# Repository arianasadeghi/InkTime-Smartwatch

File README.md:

# InkTime - Open Source Smartwatch

InkTime este un proiect de smartwatch accesibil, open-source, conceput cu un accent puternic pe eficiența energetică și autonomia bateriei. Dispozitivul este construit în jurul ecosistemului nRF52840 (oferind conectivitate Bluetooth Low Energy) și folosește un ecran E-Ink pentru a asigura o vizibilitate excelentă în lumina soarelui cu un consum de energie aproape nul în stand-by.

Acest repository conține fișierele de design hardware pentru faza **EVT (Engineering Validation Test)**.

## 1. Diagrama Bloc a Sistemului

```mermaid
graph TD
    %% Power Management
    USB[Mufă USB-C / Pogo Pins] -->|5V| CHG[IC Încărcare BQ24040]
    CHG --> BATT[Acumulator LiPo 3.7V]
    BATT --> LDO[Regulator LDO 3.3V Ultra-Low Iq]
    
    %% Core
    LDO -.->|3.3V| MCU[SoC nRF52840]
    
    %% Interfaces & Peripherals
    MCU <-->|SPI| EINK[Display E-Ink 1.54]
    MCU <-->|I2C| IMU[Accelerometru BMA400]
    MCU <-->|I2C| HR[Senzor Puls MAX30102]
    MCU -->|GPIO| VIB[Motor Vibrații]
    MCU -->|GPIO| BTN[Butoane Navigare]
    
    %% Power lines
    LDO -.->|3.3V| EINK
    LDO -.->|3.3V| IMU
    LDO -.->|3.3V| HR
```

## 2. Bill Of Materials (BOM)

Tabelul de mai jos conține componentele principale folosite în designul plăcii. Lista completă (inclusiv rezistențe și condensatoare) se găsește în fișierul .csv din folderul Manufacturing.
| Componenta | Rol în sistem | JLC Part # | Link Datasheet |
| :--- | :--- | :--- | :--- |
| **nRF52840-QIAA** | Microcontroller principal (BLE, Cortex-M4F) | C206001 | [Datasheet nRF52840](https://infocenter.nordicsemi.com/pdf/nRF52840_PS_v1.7.pdf) |
    | **BQ24040DSQR** | IC Incarcare Acumulator LiPo (1A) | C43012 | [Datasheet BQ24040](https://www.ti.com/lit/ds/symlink/bq24040.pdf) |
| **TPS7A0533PDQNR** | LDO 3.3V (Consum Quiescent extrem de mic - 1µA) | C396492 | [Datasheet TPS7A05](https://www.ti.com/lit/ds/symlink/tps7a05.pdf) |
| **BMA400** | Accelerometru Ultra-Low Power (Pedometer) | C383215 | [Datasheet BMA400](https://www.bosch-sensortec.com/media/boschsensortec/downloads/datasheets/bst-bma400-ds000.pdf) |
| **MAX30102** | Senzor Optic Puls și SpO2 | C84666 | [Datasheet MAX30102](https://www.analog.com/media/en/technical-documentation/data-sheets/MAX30102.pdf) |
| **Ecran E-Ink 1.54 inch** | Display principal (SPI) | N/A (Modul) | [Datasheet Waveshare](https://www.waveshare.com/wiki/1.54inch_e-Paper_Module) |
## 3. Descrierea Functionalitatii Hardware

### Procesare si Conectivitate:
Inima ceasului InkTime este SoC-ul Nordic nRF52840. A fost ales datorita suportului nativ pentru Bluetooth 5.0 (BLE), esential pentru sincronizarea notificarilor cu telefonul mobil. Arhitectura ARM Cortex-M4F permite procesarea eficienta a algoritmilor de numarare a pasilor si calcul al ritmului cardiac.

### Managementul Consumului de Energie (Power Tree):
Fiind un dispozitiv wearable, constrângerile de baterie sunt critice.

Sistemul este alimentat de o baterie LiPo de mici dimensiuni (ex. 200mAh).

Încărcarea se face la 5V printr-un circuit BQ24040, reglat din rezistențe pentru a oferi un curent de încărcare mic și sigur (ex. 100mA).

Pentru a coborî tensiunea la 3.3V am folosit un LDO din seria TPS7A05, care are un curent de repaus (Iq) de doar 1µA, esențial pentru a nu drena bateria când ceasul este în Deep Sleep.

### Periferice și Interfețe:

Display-ul E-Ink: Comunică prin protocol SPI. Deși are un framerate mic, este perfect pentru un ceas deoarece consumă 0mA pentru a menține imaginea afișată.

Senzorii (IMU & HR): Comunicația se realizează pe o magistrală I2C partajată. BMA400 are un mod special de "step counter" hardware care poate trezi microcontroller-ul din sleep doar când utilizatorul face un pas, economisind masiv energia.

## 4. Alocarea Pinilor nRF52840

Microcontroller-ul nRF52840 permite maparea flexibilă a pinilor (orice funcție digitală pe orice pin), lucru care a facilitat o rutare curată (fără suprapuneri) pe PCB.
| Pin nRF52840 | Nume Net / Funcție | Justificare / Detalii |
| :--- | :--- | :--- |
| **P0.13 / P0.14 / P0.15** | `SPI_SCK`, `SPI_MOSI`, `SPI_MISO` | Magistrala SPI dedicată ecranului E-Ink. Pinii au fost aleși pe aceeași latură a chip-ului cu conectorul FPC al ecranului. |
| **P0.16** | `EINK_CS` (Chip Select) | Activare magistrală SPI pentru ecran. |
| **P0.17 / P0.18** | `EINK_DC`, `EINK_RST` | Pini de control adiționali (Data/Command și Reset) necesari controller-ului de E-Ink. |
| **P0.26 / P0.27** | `I2C_SDA`, `I2C_SCL` | Magistrala I2C pentru accelerometru (BMA400) și senzorul de puls (MAX30102). Conține rezistențe de pull-up de 4.7k. |
| **P1.02** | `IMU_INT` (Interrupt) | Pin setat ca Input. BMA400 trimite un semnal aici pentru a trezi SoC-ul când detectează mișcare. |
| **P1.06** | `MOTOR_PWM` | Pin configurat ca ieșire PWM, conectat la poarta unui tranzistor MOSFET N-Channel pentru a acționa motorul de vibrații (notificări haptice). |
| **P0.11 / P0.12** | `BTN_UP`, `BTN_DOWN` | Pini conectați la butoanele laterale, configurați cu Input Pull-Up intern. |
## 5. Design Log & Integrare Mecanică (EVT Phase)

### Construcția PCB-ului: 
Cablajul a fost realizat pe 2 straturi. Pentru a asigura performanța antenei, a fost respectată zona de keepout cerută în datasheet-ul antenei ceramice (sau PCB trace), neavând planuri de masă sub aceasta.

### Constrângeri Mecanice: 
Forma PCB-ului a fost dictată strict de fișierul .step al carcasei primite. Decupajele plăcii se aliniază perfect cu pinii de montare ai carcasei.

### Stack-up 3D: 
Modelul 3D final validează faptul că placa de bază, bateria (poziționată sub PCB) și display-ul E-Ink (deasupra PCB-ului) intră în carcasa de smartwatch fără coliziuni de componente.

## 5. Calcule Detaliate de Consum de Energie (Power Budget)

Pentru a estima durata de viata a bateriei, am analizat consumul principalelor componente din circuit (nRF52840, IMU, DC/DC converter) in doua scenarii principale: Mod Activ si Mod Sleep (Standby).

### 1. Parametrii Bateriei
* Tip baterie: Li-Po
* Tensiune nominala: 3.7V
* Capacitate: 500 mAh

### 2. Consum in Mod Activ (Transmisie BLE + Achizitie Date IMU)
Cand dispozitivul este treaz, citeste date de la senzori si transmite pachete prin Bluetooth.
* nRF52840 (CPU + TX/RX la 0dBm): ~14.0 mA
* Senzor IMU (Mod Activ): ~1.0 mA
* Pierderi DC/DC Converter (Eficienta 90%): ~1.5 mA
* Total Consum Activ: ~16.5 mA

### 3. Consum in Mod Sleep (Standby / System OFF)
Cand dispozitivul nu este folosit, microcontrolerul intra in deep sleep, iar senzorii sunt trecuti in power-down.
* nRF52840 (System OFF, RAM retention): ~1.5 uA (0.0015 mA)
* Senzor IMU (Mod Power-Down): ~5.0 uA (0.005 mA)
* Quiescent Current DC/DC + LDO: ~10.0 uA (0.01 mA)
* Total Consum Sleep: ~16.5 uA (0.0165 mA)

### 4. Estimarea Duratei de Viata a Bateriei (Battery Life)

Scenariul A: Utilizare Continua (100% Mod Activ)
Daca dispozitivul ar transmite date non-stop:
* 500 mAh / 16.5 mA = 30.3 ore de functionare continua.

Scenariul B: Dispozitiv lasat pe birou (100% Mod Sleep)
Daca dispozitivul este pur si simplu lasat in stand-by:
* 500 mAh / 0.0165 mA = 30,303 ore = Aproximativ 3.4 ani.

Scenariul C: Utilizare Realista (Mix: 5% Activ, 95% Sleep)
Presupunand ca dispozitivul se trezeste periodic pentru a trimite date:
* Consum mediu = (16.5 mA * 0.05) + (0.0165 mA * 0.95) = 0.825 mA + 0.015 mA = 0.84 mA

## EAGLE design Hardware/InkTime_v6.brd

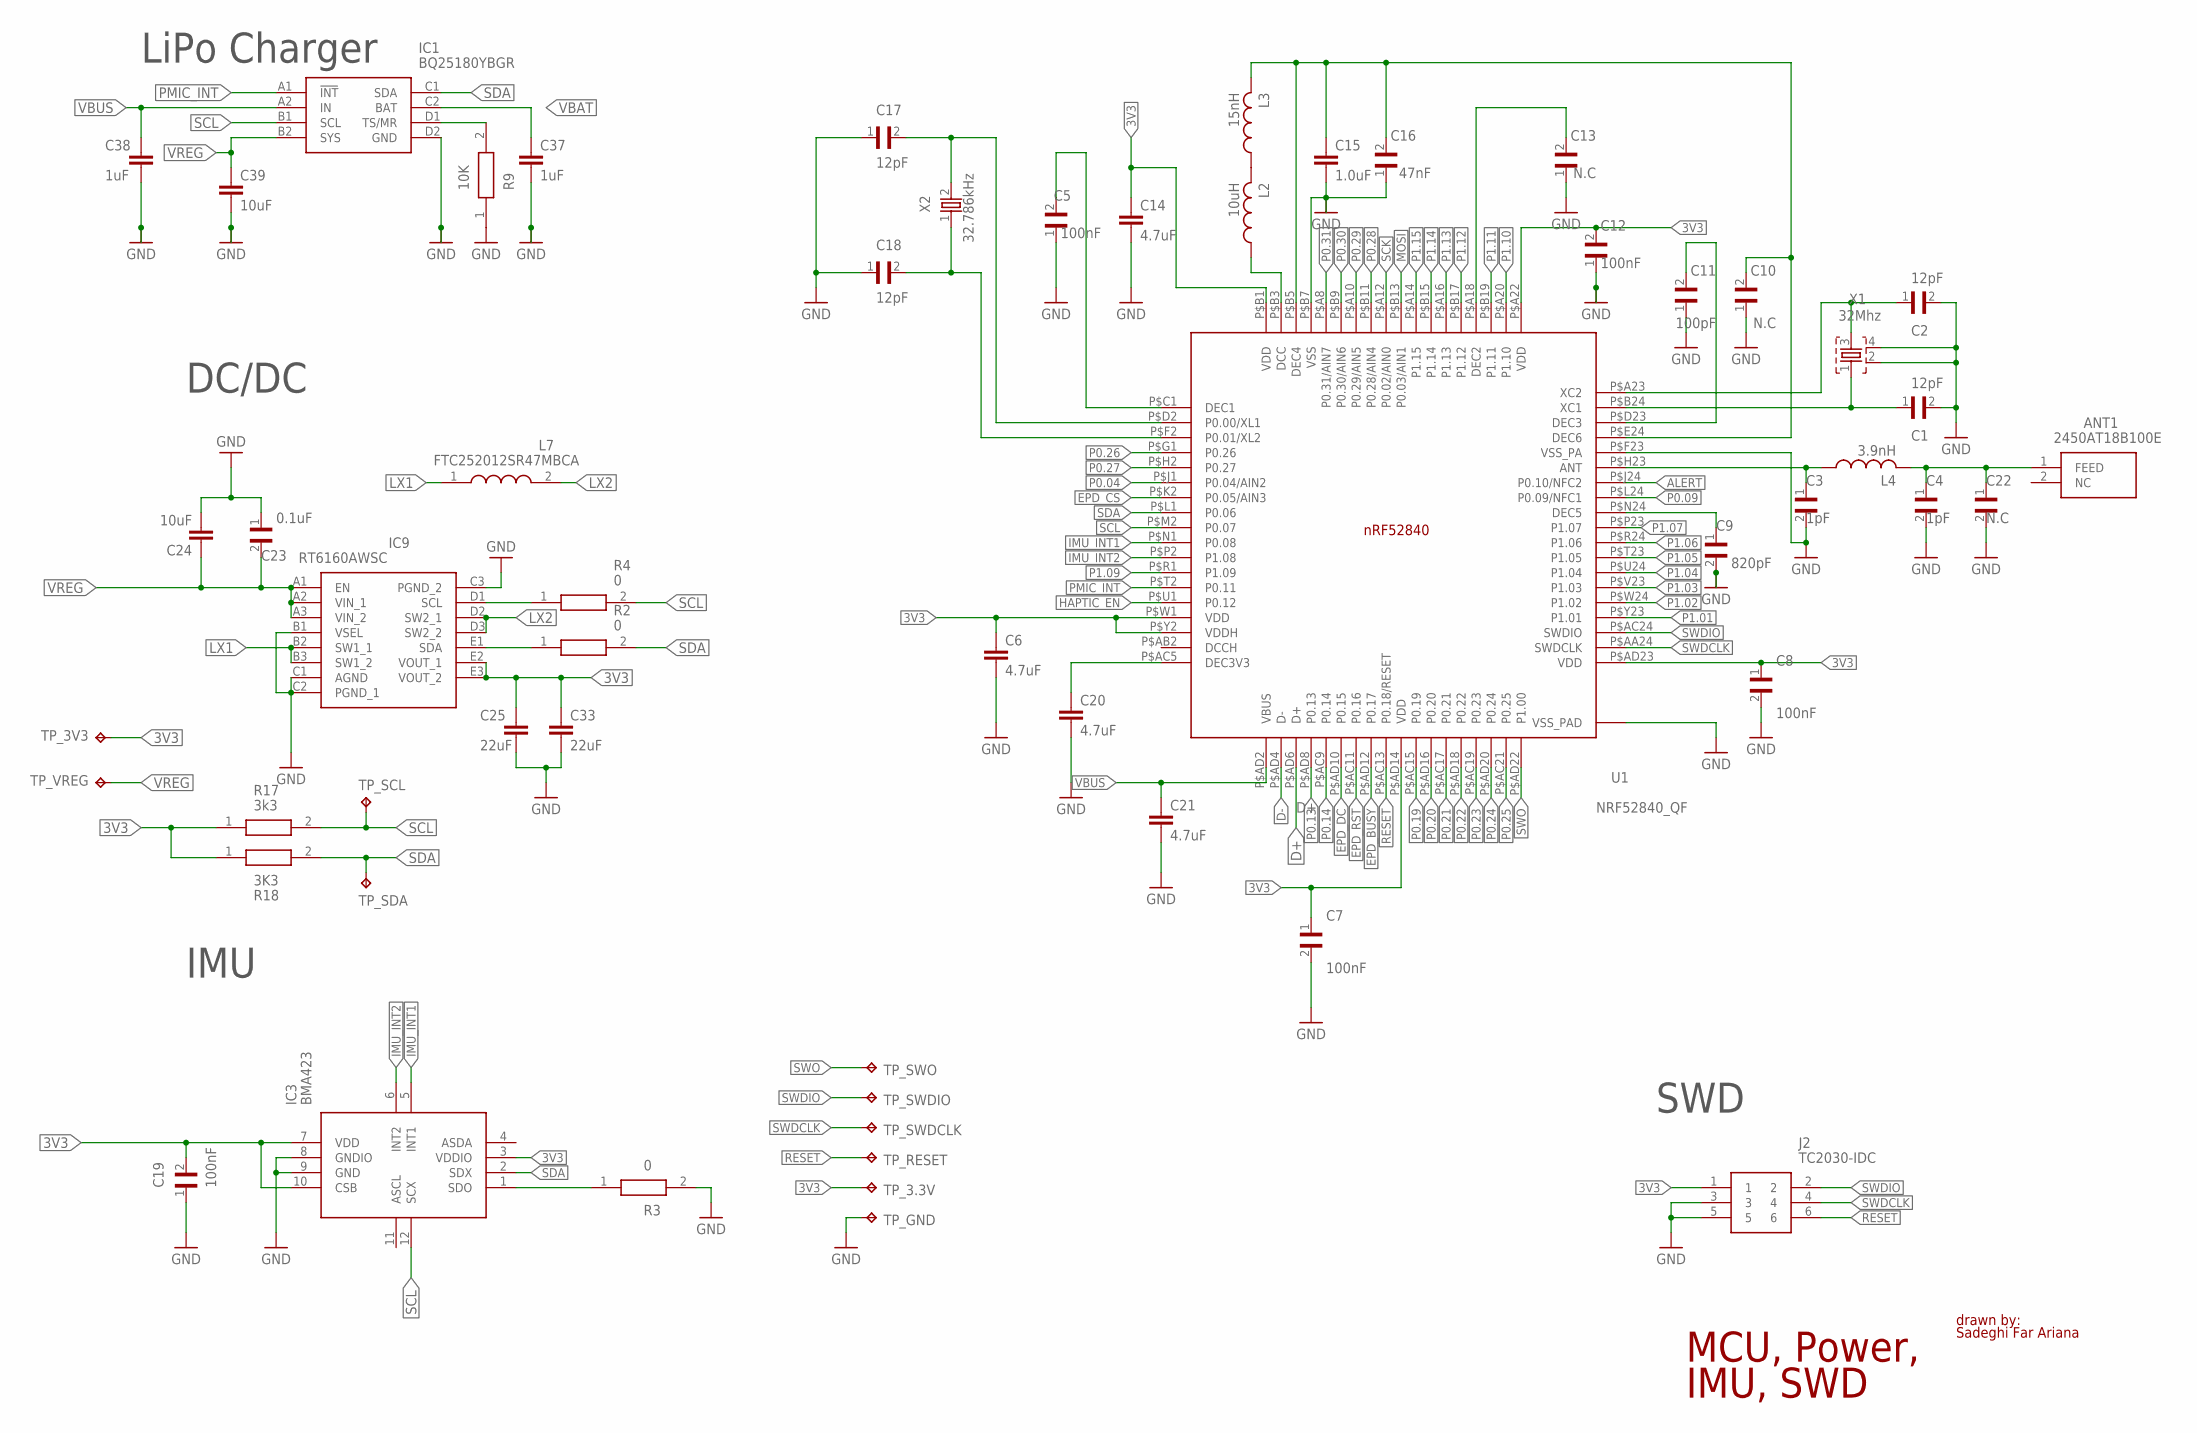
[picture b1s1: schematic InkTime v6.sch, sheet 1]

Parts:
ANT1: 2450AT18B100E; 2450AT18B100E_ANTC3216X140N
C1, C2, C17, C18: 12pF; GRM011R60J152KE01L_1_0201
C3, C4: 1pF; GRM011R60J152KE01L_1_0201
C5, C7, C8, C12, C19: 100nF; GRM011R60J152KE01L_1_0201
C6, C14, C20, C21: 4.7uF; ESP32_C6_LIBRARY_1_ESP32_WROVER_EAGLE-LTSPICE_C0402
C9: 820pF; GRM011R60J152KE01L_1_0201
C10, C13, C22: N.C; GRM011R60J152KE01L_1_0201
C11: 100pF; GRM011R60J152KE01L_1_0201
C15: 1.0uF; ESP32_C6_LIBRARY_1_ESP32_WROVER_EAGLE-LTSPICE_C0402
C16: 47nF; GRM011R60J152KE01L_1_0201
C23: 0.1uF; GRM011R60J152KE01L_1_0201
C24: 10uF; ESP32_C6_LIBRARY_1_ESP32_WROVER_EAGLE-LTSPICE_C0402
C25, C33: 22uF; ESP32_C6_LIBRARY_1_ESP32_WROVER_EAGLE-LTSPICE_C0402
C37, C38: 1uF; PERFECT_0402_0402
C39: 10uF; PERFECT_0402_0402
IC1: BQ25180YBGR; BQ25180YBGR_BGA8C40P2X4_100X155X50
IC3: BMA423; BMA423_BMA423
IC9: RT6160AWSC; RT6160AWSC_BGA15C40P3X5_140X230X60
J2: TC2030-IDC; TC2030-IDC_TC2030IDC
L2: 10uH; NORDIC_NRF_2_RESC0402_L
L3: 15nH; NORDIC_NRF_2_RESC0402_L
L4: 3.9nH; NORDIC_NRF_2_RESC0402_L
L7: FTC252012SR47MBCA; MLP2016SR47MT0S1_INDC2016X100N
R2, R3, R4: 0; CPF0201D7K68C1_0201
R9: 10K; ERA-1AEB3401C_0201
R17: 3k3; CPF0201D7K68C1_0201
R18: 3K3; CPF0201D7K68C1_0201
TP_3.3V, TP_3V3: HECTOR_WATCH_1_TPTP20R; HECTOR_WATCH_1_TP20R
TP_GND: HECTOR_WATCH_1_TPTP20R; HECTOR_WATCH_1_TP20R
TP_RESET: HECTOR_WATCH_1_TPTP20R; HECTOR_WATCH_1_TP20R
TP_SCL: HECTOR_WATCH_1_TPTP20R; HECTOR_WATCH_1_TP20R
TP_SDA: HECTOR_WATCH_1_TPTP20R; HECTOR_WATCH_1_TP20R
TP_SWDCLK: HECTOR_WATCH_1_TPTP20R; HECTOR_WATCH_1_TP20R
TP_SWDIO: HECTOR_WATCH_1_TPTP20R; HECTOR_WATCH_1_TP20R
TP_SWO: HECTOR_WATCH_1_TPTP20R; HECTOR_WATCH_1_TP20R
TP_VREG: HECTOR_WATCH_1_TPTP20R; HECTOR_WATCH_1_TP20R
U1: NRF52840_QF; NORDIC_NRF_4_AQFN50P700X700X85_HS-74N
X1: 32Mhz; NORDIC_NRF_BT-XTAL_2016_N
X2: 32.786kHz; NORDIC_NRF_1_XTAL_3215_N

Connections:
3V3: C6.1, C7.1, C8.1, C12.2, C14.1, C19.2, C25.1, C33.1, IC3.3 (VDDIO), IC3.7 (VDD), IC3.10 (CSB), IC9.E2 (VOUT_1), IC9.E3 (VOUT_2), J2.1, R17.1, R18.1, TP_3.3V.TP, TP_3V3.TP, U1.P$A22 (VDD), U1.P$AD14 (VDD), U1.P$AD23 (VDD), U1.P$B1 (VDD), U1.P$W1 (VDD), U1.P$Y2 (VDDH); also elsewhere on the board
ALERT: U1.P$J24 (P0.10/NFC2); also elsewhere on the board
D+: U1.P$AD6 (D+); also elsewhere on the board
D-: U1.P$AD4 (D-); also elsewhere on the board
EPD_BUSY: U1.P$AD12 (P0.17); also elsewhere on the board
EPD_CS: U1.P$K2 (P0.05/AIN3); also elsewhere on the board
EPD_DC: U1.P$AD10 (P0.15); also elsewhere on the board
EPD_RST: U1.P$AC11 (P0.16); also elsewhere on the board
HAPTIC_EN: U1.P$U1 (P0.12); also elsewhere on the board
IMU_INT1: IC3.5 (INT1), U1.P$N1 (P0.08)
IMU_INT2: IC3.6 (INT2), U1.P$P2 (P1.08)
LX1: IC9.B2 (SW1_1), IC9.B3 (SW1_2), L7.1
LX2: IC9.D2 (SW2_1), IC9.D3 (SW2_2), L7.2
MOSI: U1.P$B13 (P0.03/AIN1); also elsewhere on the board
unnamed: L2.2, L3.1
unnamed: IC1.D1 (TS/MR), R9.2
unnamed: IC9.E1 (SDA), R2.1
unnamed: IC9.D1 (SCL), R4.1
unnamed: IC3.1 (SDO), R3.1
unnamed: C9.1, U1.P$N24 (DEC5)
unnamed: C3.1, L4.1, U1.P$H23 (ANT)
unnamed: ANT1.1 (FEED), C4.1, C22.1, L4.2
unnamed: C11.2, U1.P$D23 (DEC3)
unnamed: C1.1, U1.P$B24 (XC1), X1.1
unnamed: C2.1, U1.P$A23 (XC2), X1.3
unnamed: C10.2, C15.1, C16.2, L3.2, U1.P$B5 (DEC4), U1.P$E24 (DEC6)
unnamed: C13.2, U1.P$A18 (DEC2)
unnamed: L2.1, U1.P$B3 (DCC)
unnamed: C5.2, U1.P$C1 (DEC1)
unnamed: C17.2, U1.P$D2 (P0.00/XL1), X2.2
unnamed: C18.2, U1.P$F2 (P0.01/XL2), X2.1
unnamed: C20.1, U1.P$AC5 (DEC3V3)
P0.04: U1.P$J1 (P0.04/AIN2)
P0.09: U1.P$L24 (P0.09/NFC1)
P0.13: U1.P$AD8 (P0.13); also elsewhere on the board
P0.14: U1.P$AC9 (P0.14); also elsewhere on the board
P0.19: U1.P$AC15 (P0.19)
P0.20: U1.P$AD16 (P0.20)
P0.21: U1.P$AC17 (P0.21)
P0.22: U1.P$AD18 (P0.22)
P0.23: U1.P$AC19 (P0.23)
P0.24: U1.P$AD20 (P0.24)
P0.25: U1.P$AC21 (P0.25)
P0.26: U1.P$G1 (P0.26)
P0.27: U1.P$H2 (P0.27)
P0.28: U1.P$B11 (P0.28/AIN4)
P0.29: U1.P$A10 (P0.29/AIN5)
P0.30: U1.P$B9 (P0.30/AIN6)
P0.31: U1.P$A8 (P0.31/AIN7)
P1.01: U1.P$Y23 (P1.01); also elsewhere on the board
P1.02: U1.P$W24 (P1.02); also elsewhere on the board
P1.03: U1.P$V23 (P1.03)
P1.04: U1.P$U24 (P1.04)
P1.05: U1.P$T23 (P1.05)
P1.06: U1.P$R24 (P1.06)
P1.07: U1.P$P23 (P1.07)
P1.09: U1.P$R1 (P1.09)
P1.10: U1.P$A20 (P1.10)
P1.11: U1.P$B19 (P1.11)
P1.12: U1.P$B17 (P1.12)
P1.13: U1.P$A16 (P1.13)
P1.14: U1.P$B15 (P1.14)
P1.15: U1.P$A14 (P1.15)
PMIC_INT: IC1.A1 (!INT), U1.P$T2 (P0.11)
RESET: J2.6, TP_RESET.TP, U1.P$AC13 (P0.18/RESET)
SCK: U1.P$A12 (P0.02/AIN0); also elsewhere on the board
SCL: IC1.B1 (SCL), IC3.12 (SCX), R4.2, R17.2, TP_SCL.TP, U1.P$M2 (P0.07); also elsewhere on the board
SDA: IC1.C1 (SDA), IC3.2 (SDX), R2.2, R18.2, TP_SDA.TP, U1.P$L1 (P0.06); also elsewhere on the board
SWDCLK: J2.4, TP_SWDCLK.TP, U1.P$AA24 (SWDCLK)
SWDIO: J2.2, TP_SWDIO.TP, U1.P$AC24 (SWDIO)
SWO: TP_SWO.TP, U1.P$AD22 (P1.00)
VBAT: C37.1, IC1.C2 (BAT); also elsewhere on the board
VBUS: C21.1, C38.1, IC1.A2 (IN), U1.P$AD2 (VBUS); also elsewhere on the board
VREG: C23.2, C24.1, C39.1, IC1.B2 (SYS), IC9.A1 (EN), IC9.A2 (VIN_1), IC9.A3 (VIN_2), TP_VREG.TP

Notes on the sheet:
drawn by: Sadeghi Far Ariana
MCU, Power, IMU, SWD
LiPo Charger
DC/DC
IMU
SWD

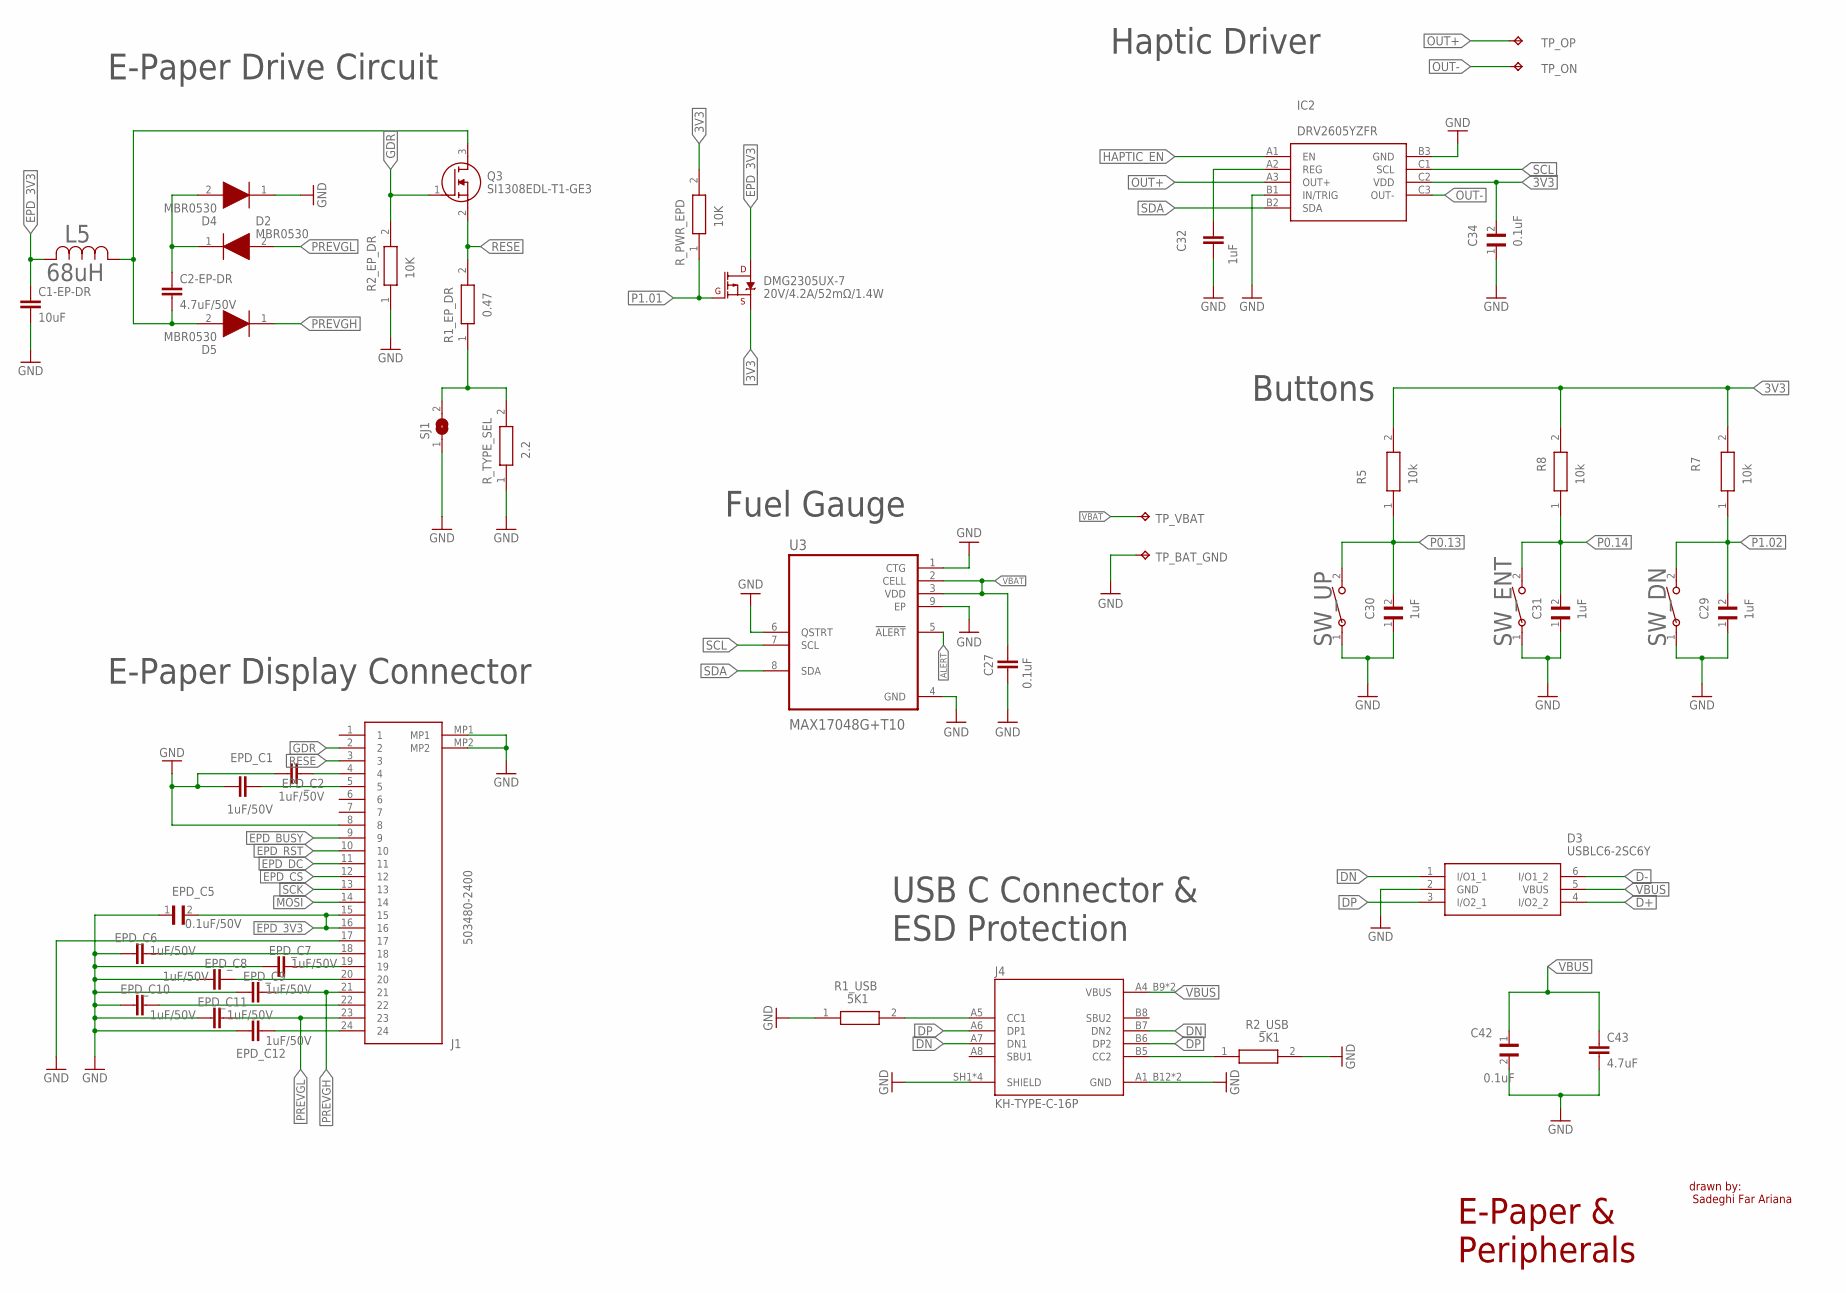
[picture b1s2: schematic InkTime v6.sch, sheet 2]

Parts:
C1-EP-DR: 10uF; ESP32_C6_LIBRARY_1_ESP32_WROVER_EAGLE-LTSPICE_C0402
C2-EP-DR: 4.7uF/50V; ESP32_C6_LIBRARY_1_ESP32_WROVER_EAGLE-LTSPICE_C0402
C27: 0.1uF; NORDIC_NRF_3_RESC0201_L
C29, C30, C31: 1uF; GRM011R60J152KE01L_2_CAPC0201X13N
C32: 1uF; ESP32_C6_LIBRARY_1_ESP32_WROVER_EAGLE-LTSPICE_C0402
C34, C42: 0.1uF; GRM011R60J152KE01L_2_CAPC0201X13N
C43: 4.7uF; ESP32_C6_LIBRARY_1_ESP32_WROVER_EAGLE-LTSPICE_C0402
D2, D4, D5: MBR0530; ESP32_C6_LIBRARY_5_SOD3716X135N
D3: USBLC6-2SC6Y; ESP32_C6_LIBRARY_3_SOT95P280X145-6N
DMG2305UX-7: 20V/4.2A/52mΩ/1.4W; ESP32_C6_LIBRARY_4_ESP32_C6_LIBRARY_4_ESP32_C6_LIBRARY_4_ES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
EPD_C1, EPD_C2: 1uF/50V; ESP32_C6_LIBRARY_1_ESP32_WROVER_EAGLE-LTSPICE_C0402
EPD_C5: 0.1uF/50V; GRM011R60J152KE01L_2_CAPC0201X13N
EPD_C6, EPD_C7, EPD_C8, EPD_C9, EPD_C10, EPD_C11, EPD_C12: 1uF/50V; NORDIC_NRF_3_RESC0402_L
IC2: DRV2605YZFR; DRV2605YZFR_BGA9C50P3X3_144X144X62
J1: 503480-2400; 503480-2400_5034802400
J4: KH-TYPE-C-16P; KH-TYPE-C-16P_KINGHELM_KH-TYPE-C-16P
L5: 68uH; ESP32_C6_LIBRARY_2_IND_4828-WE-TPC_WRE
Q3: SI1308EDL-T1-GE3; ESP32_C6_LIBRARY_6_SOT65P210X110-3N
R1_EP_DR: 0.47; CPF0201D7K68C1_0201
R1_USB, R2_USB: 5K1; CPF0201D7K68C1_0201
R2_EP_DR: 10K; CPF0201D7K68C1_0201
R5, R7, R8: 10k; CPF0201D7K68C1_0201
R_PWR_EPD: 10K; CPF0201D7K68C1_0201
R_TYPE_SEL: 2.2; CPF0201D7K68C1_0201
SJ1: ESP32_C6_LIBRARY_7_JUMPER_SJ
SW_DN: 2025-10-22_07-23-44_LIBRARY_EVP-AKE31ASW_EVP-AKE3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; 2025-10-22_07-23-44_LIBRARY_SW_EVP-AKE31A_PAN
SW_ENT: 2025-10-22_07-23-44_LIBRARY_EVP-AKE31ASW_EVP-AKE3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; 2025-10-22_07-23-44_LIBRARY_SW_EVP-AKE31A_PAN
SW_UP: 2025-10-22_07-23-44_LIBRARY_EVP-AKE31ASW_EVP-AKE3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; 2025-10-22_07-23-44_LIBRARY_SW_EVP-AKE31A_PAN
TP_BAT_GND: HECTOR_WATCH_1_TPTP20R; HECTOR_WATCH_1_TP20R
TP_ON: HECTOR_WATCH_1_TPTP20R; HECTOR_WATCH_1_TP20R
TP_OP: HECTOR_WATCH_1_TPTP20R; HECTOR_WATCH_1_TP20R
TP_VBAT: HECTOR_WATCH_1_TPTP20R; HECTOR_WATCH_1_TP20R
U3: MAX17048G+T10; ESP32_C6_LIBRARY_SON50P200X200X80-9N

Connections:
3V3: C34.2, DMG2305UX-7.2 (S), IC2.C2 (VDD), R5.2, R7.2, R8.2, R_PWR_EPD.2; also elsewhere on the board
ALERT: U3.5 (!ALERT); also elsewhere on the board
D+: D3.4 (I/O2_2); also elsewhere on the board
D-: D3.6 (I/O1_2); also elsewhere on the board
DN: D3.1 (I/O1_1), J4.A7 (DN1), J4.B7 (DN2)
DP: D3.3 (I/O2_1), J4.A6 (DP1), J4.B6 (DP2)
EPD_3V3: C1-EP-DR.1, DMG2305UX-7.3 (D), EPD_C5.2, J1.15, J1.16, L5.2
EPD_BUSY: J1.9; also elsewhere on the board
EPD_CS: J1.12; also elsewhere on the board
EPD_DC: J1.11; also elsewhere on the board
EPD_RST: J1.10; also elsewhere on the board
GDR: J1.2, Q3.1 (G), R2_EP_DR.2
HAPTIC_EN: IC2.A1 (EN); also elsewhere on the board
MOSI: J1.14; also elsewhere on the board
unnamed: C32.1, IC2.A2 (REG)
unnamed: J4.B5 (CC2), R2_USB.1
unnamed: J4.A5 (CC1), R1_USB.2
unnamed: C2-EP-DR.2, D5.2 (A), L5.1, Q3.3 (D)
unnamed: EPD_C2.2, J1.4
unnamed: EPD_C1.2, J1.5
unnamed: C2-EP-DR.1, D2.1 (K), D4.2 (A)
unnamed: EPD_C6.2, J1.18
unnamed: EPD_C7.2, J1.19
unnamed: EPD_C8.2, J1.20
unnamed: R1_EP_DR.1, R_TYPE_SEL.2, SJ1.2
unnamed: EPD_C10.2, J1.22
unnamed: EPD_C12.2, J1.24
OUT+: IC2.A3 (OUT+), TP_OP.TP
OUT-: IC2.C3 (OUT-), TP_ON.TP
P0.13: C30.2, R5.1, SW_UP.2; also elsewhere on the board
P0.14: C31.2, R8.1, SW_ENT.2; also elsewhere on the board
P1.01: DMG2305UX-7.1 (G), R_PWR_EPD.1; also elsewhere on the board
P1.02: C29.2, R7.1, SW_DN.2; also elsewhere on the board
PREVGH: D5.1 (K), EPD_C9.2, J1.21
PREVGL: D2.2 (A), EPD_C11.2, J1.23
RESE: J1.3, Q3.2 (S), R1_EP_DR.2
SCK: J1.13; also elsewhere on the board
SCL: IC2.C1 (SCL), U3.7 (SCL); also elsewhere on the board
SDA: IC2.B2 (SDA), U3.8 (SDA); also elsewhere on the board
VBAT: C27.1, TP_VBAT.TP, U3.2 (CELL), U3.3 (VDD); also elsewhere on the board
VBUS: C42.1, C43.1, D3.5 (VBUS), J4.A4_B9 (VBUS), J4.A9_B4 (VBUS); also elsewhere on the board

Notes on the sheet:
Buttons
Haptic Driver
Fuel Gauge
drawn by: Sadeghi Far Ariana
E-Paper & Peripherals
USB C Connector & ESD Protection
E-Paper Display Connector
E-Paper Drive Circuit

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
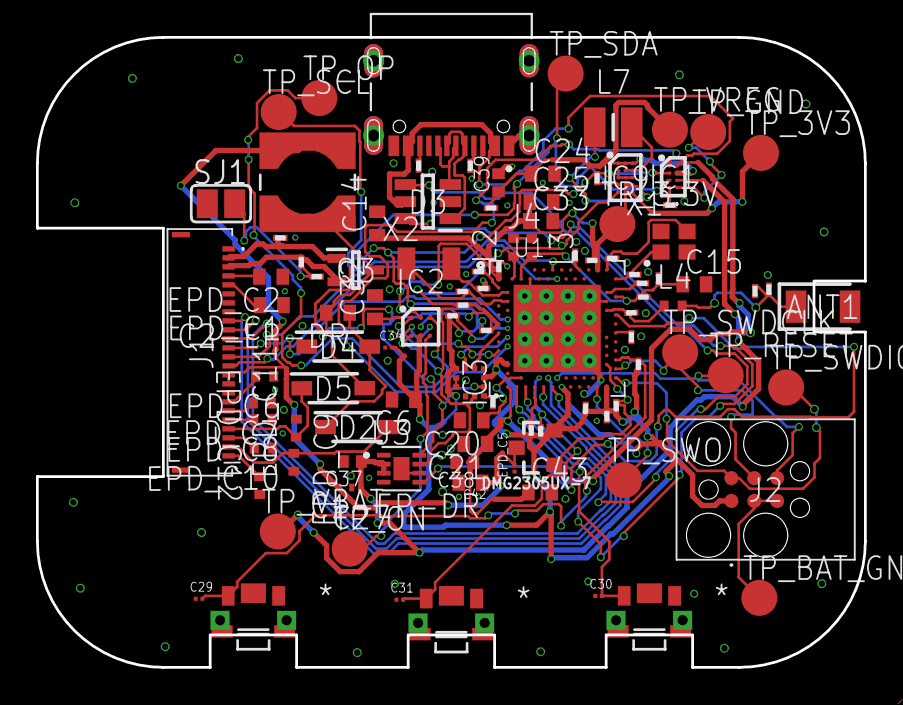
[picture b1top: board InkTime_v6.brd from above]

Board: 2 copper layers, 46.0 x 35.0 mm, 105 parts (0 on the bottom side), 70 nets.

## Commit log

2026-04-10 Add files via upload
    Fixed README
2026-04-10 Add files via upload
    Fixed README.2
2026-04-10 Enhance README with project details and diagrams
    Updated README.md to include additional details about the InkTime smartwatch project, including system block diagram, BOM, hardware functionality, pin allocation, and mechanical integration.
2026-04-10 Revise README.md with project details and diagrams
    Updated README.md to include additional sections and details about the InkTime smartwatch project.
2026-04-10 Add files via upload
    Added IMAGES folder
2026-04-15 Add files via upload
    Added Mechanical folder and Schematic.pdf in Hardware folder
2026-04-20 Add files via upload
    Fixed PCB
2026-04-20 Enhance README with power budget and design details
    Updated README.md to include additional sections and detailed power consumption estimates for the InkTime smartwatch project.

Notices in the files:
parts and their libraries:
InkTime_v5: COPYRIGHT: Copyright (C) 2025 Ultra Librarian. All rights reserved.
InkTime_v5: COPYRIGHT: Copyright (C) 2024 Ultra Librarian. All rights reserved.
